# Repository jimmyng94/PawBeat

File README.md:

# PawPulse

PawPulse is an [open-source](https://github.com/jimmyng94/PawPulse/blob/master/LICENSE) pet health monitoring project developed by Engineering MSc students at the University Of Glasgow using a Raspberry Pi. The main functions that the project provide are:
- Heartbeat Monitoring
- Pedometer
- Live data display through a [website](https://tymonherzyk.github.io/PawPulseWeb/)

Currently, the development of the project is only intended for use on a dog. Usage on other pets will require further testing.

## Project Architecture

#### Hardware
All the sensors along with the raspberry will be attached to a dog harness to collect and process the data before posting the data to the web page. Therefore, the PCB is split into 2 individual boards. The 1st board is a PiHat where the [IMU](https://www.st.com/resource/en/datasheet/lsm6ds3.pdf) is located. The 2nd board contains the [ADC](http://www.ti.com/lit/ds/symlink/ads1015.pdf) and is located beside the microphone. Both boards are using I2C to communicate with the Raspberry Pi.

#### Software
The PawPulse software is split into two main files **pawpulse.cpp** and **pawpulseWebClient.cpp**. The pawpulse file is responsible for aquiring data for the dog's heartbeat and step count from the corresponding hardware. Once the data has been aquired through the getBPM() and getStep() functions it is then passed to the writeBPM() and writeSTEP() functions. These functions sort the data into the correct JSON format and pass it to the pawpulseWebClient.cpp file through named pipes bpm_fifo and step_fifo. The pawpulseWebClient file is responsible for uploading the data to the PawPulse website through the PubNub API. Threading has been used throughout the software to allow both processes (bpm and step) to work at the same time.  

#### Website
A website has been built in order to test the web capabilities of this project. The website has been designed to function as a profesional space in which the data from the PawPulse system can be displayed to users in real-time. The website has been built using HTML, CSS and JavaScript languages. To display data in real-time it utlises libraries such as PubNub API and EON. The website has also been built to be responsive and hence can be viewed safely on phone and monitors. Example screenshots from the "Live Data" page are given below:

The PawPulse website is hosted at https://tymonherzyk.github.io/PawPulseWeb/

#### Guides
Further information as well as in-depth installation and development guides for this project can be found on our Github [Wiki](https://github.com/jimmyng94/PawPulse/wiki) Page.

## Quick Installation
A full in-depth installation guide is available in our [wiki](https://github.com/jimmyng94/PawPulse/wiki/Installation-Guide).

#### 1. Clone PawPulse github repository
On the main repository page, click the green "Clone or Download" button, copy the address that drops down. In your chosen directory clone the PawPulse repository by running the folowing code:
```
git clone *copied address*
```
#### 2. Install required libraries
Install the required libraries (see the wiki for more information):
* ADS1015 Library
* LSM6DS3 Library
* Fir1 Library
* PubNub c-core
* WiringPi

#### 3. Make the pawpulse.cpp executable
To make the pawpulse executable file navigate into the "Software" folder and use the "CMakeLists.txt" file. This is done by running the following code:
```
cmake .
make
```
A new executable with the name **pawpulse** should now be available in the "Software" folder.

#### 4. Make the pawpulseWebClient.cpp executable
To make the pawpulseWebClient executable file navigate into the "Software" folder and use the "pawpulseWebClient.mk" makefile. This is done by running the following code:
```
make -f pawpulseWebClient.mk
```
A new executable with the name **pawpulseWebClient** should now be available in the "Software" folder.

#### 5. Run software
To run both executables simply run the following code in the "Software" folder using two seprate command lines:
```
./pawpulseWebClient
```
```
./pawpulse
```
## Additional Functionality
Recommendations of possible functions that could be added in the future: 
- Automated execution of the PawPulse software.
- Live heartbeat playback allowing the owner to hear their pet's heartbeat and make it more convenient for a veterinarian to monitor pets
- GPS tracking
- Health diagnoses and recommendations
- Personalised website login
- Phone application development for convenience

## Demonstration
A demonstration of the real-time application and operation of the PawPulse software is available on the PawPulse [Youtube Channel](https://www.youtube.com/channel/UC-eADsYPdyjXFOSjoH-YVWg). The demonstration shows the software being executed and the data being uploaded to the PawPulse website in real-time.

Video Link - https://www.youtube.com/watch?v=mI9MpOQwHOM

## Social Media
- [Instagram](https://www.instagram.com/paw_pulse/)
- [Youtube](https://www.youtube.com/channel/UC-eADsYPdyjXFOSjoH-YVWg)
- [Twitter](https://twitter.com/paw_pulse)

## Authors 
- [Maggie Wood](https://github.com/maggwood) - Data acquisition and data filtering
- [Ng Jing Ming](https://github.com/jimmyng94) - Hardware and hardware/software communication
- [Tymon Herzyk](https://github.com/tymonherzyk) - IPC, web client and website

## Disclaimer
Disruption due to COVID-19 has prohibited us from running any actual tests on our test dog. Thus, this project is not guaranteed to work on a dog. Testing was only done using a human heartbeat that was collected before the disruption. In the future we hope to be able to test it on a real pet and collect more data to improve our algorithm. Thank you for your understanding.

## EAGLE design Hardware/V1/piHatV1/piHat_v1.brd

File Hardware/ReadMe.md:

# Hardware
Hardware development of this project went through a few development and testing to determine the best circuit used for this project. 
This project requires an analog to digital converter to convert the analog microphone signal and an inertial measurement unit for pedometer function. 
The selected component used for version 1 of this project is listed below.
The schematic, board design and PCB mask are included in the newest version.  

## Version 0 (Concept)
- Mic signal is passed through a 4th order Low pass filter that filters noise above 1kHz. Used a [LM324N](http://www.ti.com/lit/ds/symlink/lm324-n.pdf). All the components are located in MicBOB_V0. 
- The IMU selected is attached on a PiHat. Fairly straight forward
###### Problems
- The Low pass filter seems to be attenuating the signal and no signal reaches the ADC.
- Missing power line to the VCC of the IMU.

## Version 1 (Prototype A)
- Removed the Low Pass Filter and used the ADS1014 Programmable Gain Amplifier(PGA) to amplify the signal from the microphone.
- Added a diode for reverse voltage protection.
- Added a trace to supply power to the IMU.

| Part | Quantity|
|-----| :-----: |
|Raspberry Pi | 1|
|[ADC ADS1014](http://www.ti.com/lit/ds/symlink/ads1015.pdf)|1|
|[IMU LSM6DS3](https://www.st.com/resource/en/datasheet/lsm6ds3.pdf)|1|
|6mm Microphone|1|
|1206 0.1uf Capacitor |2|
|5K Resistor|4|
|1N4148 Diode|1|
|20-pin Female Header|1|
|6-way header Molex connector|2|
|6-way shell Molex connector|2|
|M2.5 Standoffs	|4|
|M2.5 Screws	|4|

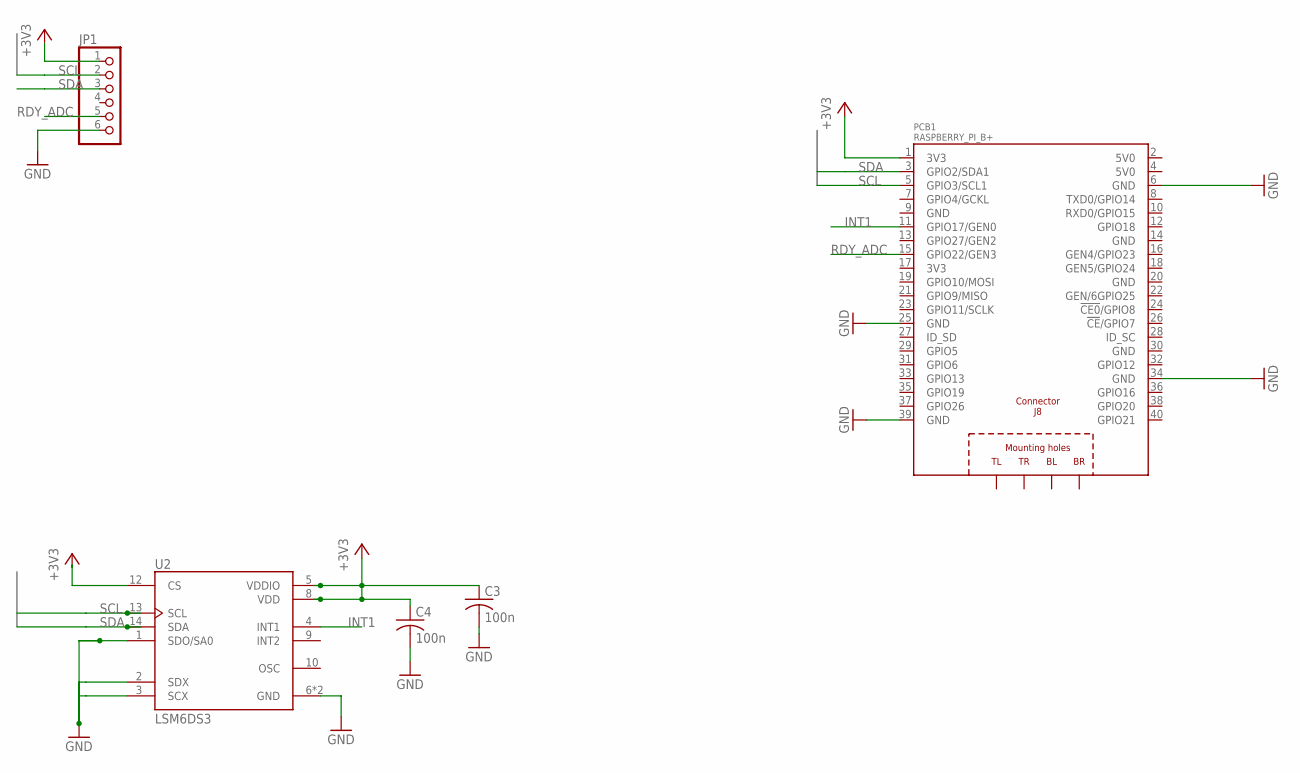
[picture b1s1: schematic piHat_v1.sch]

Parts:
C3, C4: 100n; C1206
JP1: PINHD-1X6; 1X06
PCB1: RASPBERRY_PI_B+
U2: LSM6DS3; PQFN50P300X250X86-14N

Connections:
+3V3: C3.1, C4.1, JP1.1, PCB1.1 (3V3), U2.5 (VDDIO), U2.8 (VDD), U2.12 (CS)
GND: C3.2, C4.2, JP1.6, PCB1.6 (GND), PCB1.25 (GND), PCB1.39 (GND), U2.1 (SDO/SA0), U2.2 (SDX), U2.3 (SCX), U2.6 (GND), U2.7 (GND)
GND@7: PCB1.34 (GND)
INT1: PCB1.11 (GPIO17/GEN0), U2.4 (INT1)
RDY_ADC: JP1.5, PCB1.15 (GPIO22/GEN3)
SCL: JP1.2, PCB1.5 (GPIO3/SCL1), U2.13 (SCL)
SDA: JP1.3, PCB1.3 (GPIO2/SDA1), U2.14 (SDA)

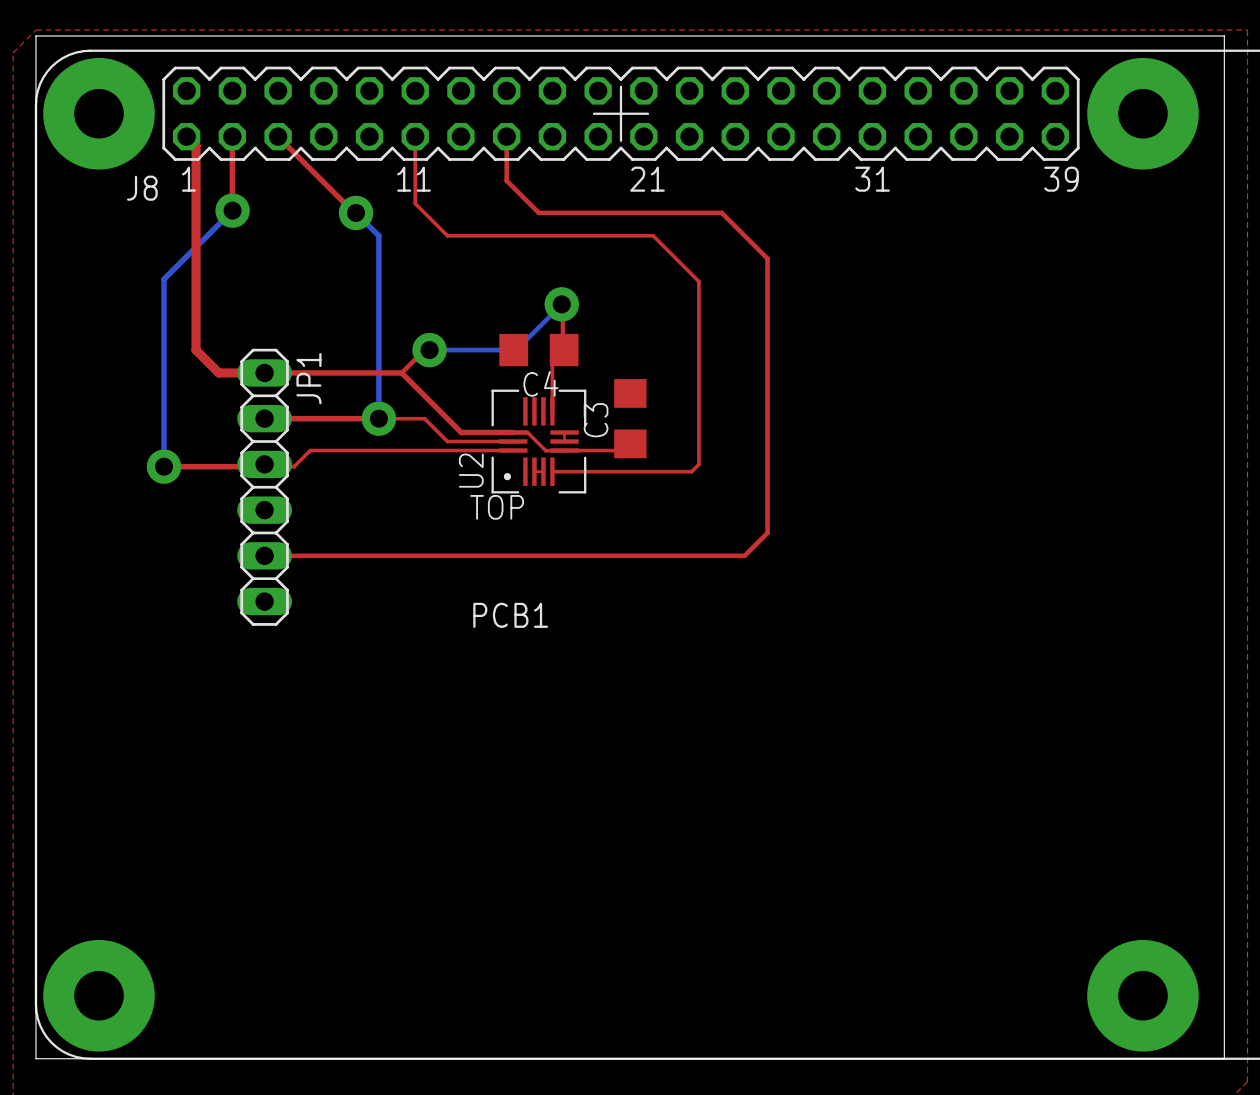
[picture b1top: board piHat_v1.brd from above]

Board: 2 copper layers, 66.0 x 56.8 mm, 5 parts (0 on the bottom side), 6 nets.

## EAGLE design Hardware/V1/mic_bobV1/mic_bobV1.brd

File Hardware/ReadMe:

Contain all the version of sensor and testing to main board intergration

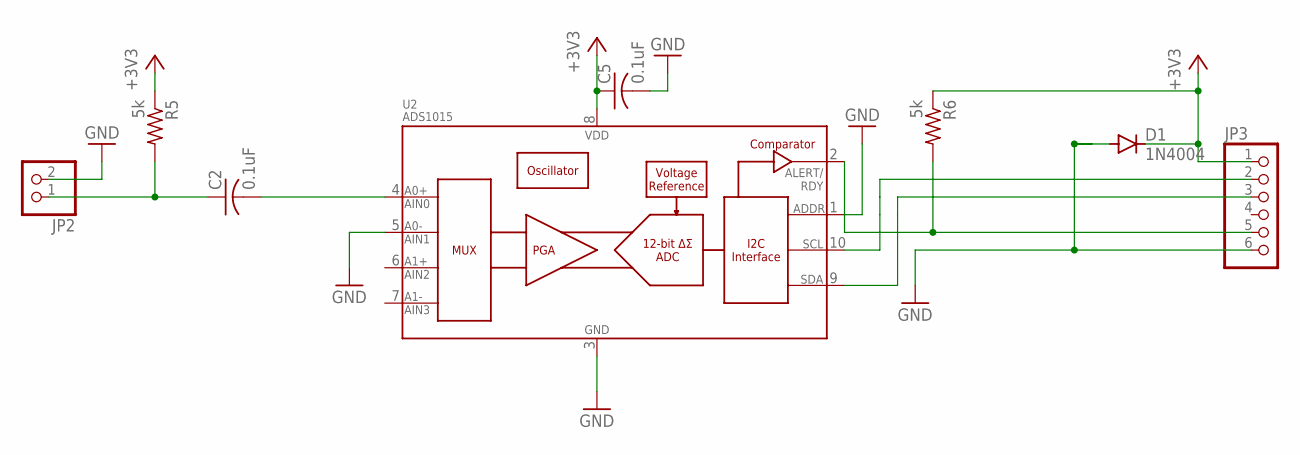
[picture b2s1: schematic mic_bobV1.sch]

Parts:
C2, C5: 0.1uF; C1206
D1: 1N4004; DO41-10
JP2: PINHD-1X2; 1X02
JP3: PINHD-1X6; 1X06
R5, R6: 5k; 0207/10
U2: ADS1015; MSOP10

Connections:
+3V3: C5.1, D1.C, JP3.1, R5.1, R6.1, U2.8 (VDD)
GND: C5.2, D1.A, JP2.2, JP3.6, U2.1 (ADDR), U2.3 (VSS), U2.5 (AIN1)
unnamed: C2.1, JP2.1, R5.2
unnamed: C2.2, U2.4 (AIN0)
unnamed: JP3.5, R6.2, U2.2 (ALERT/RDY)
unnamed: JP3.2, U2.10 (SCL)
unnamed: JP3.3, U2.9 (SDA)

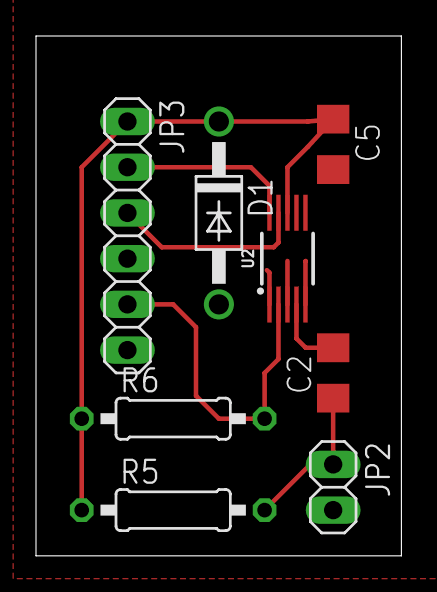
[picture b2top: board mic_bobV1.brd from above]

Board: 2 copper layers, 20.3 x 28.9 mm, 8 parts (0 on the bottom side), 7 nets.

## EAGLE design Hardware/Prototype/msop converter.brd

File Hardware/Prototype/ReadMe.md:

# Hardware Development
* After some consideration of device that are suitable for this project there are the ADS1014 is selected and the LSM6DS3 is selected. 
* To test the ADC a breakoutboard (msop10.brd) is develop for quick testing.
* The IMU used for initial testing is purchased from [sparkfun](https://www.sparkfun.com/products/13339)

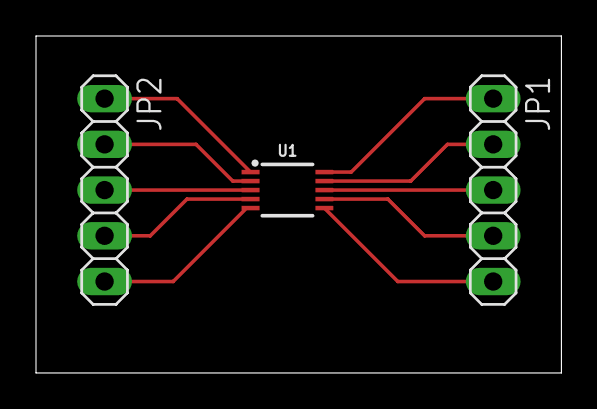
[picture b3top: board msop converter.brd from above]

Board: 2 copper layers, 29.2 x 18.7 mm, 3 parts (0 on the bottom side), 10 nets.

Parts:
JP1, JP2: 1X05
U1: ADS1015; MSOP10

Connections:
unnamed: JP2.1, U1.1
unnamed: JP2.2, U1.2
unnamed: JP2.3, U1.3
unnamed: JP2.4, U1.4
unnamed: JP2.5, U1.5
unnamed: JP1.1, U1.10
unnamed: JP1.2, U1.9
unnamed: JP1.3, U1.8
unnamed: JP1.4, U1.7
unnamed: JP1.5, U1.6

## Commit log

2020-02-05 Add files via upload
    Slides for initial presentation as given on the 29/01/2020
2020-02-05 Create mic2i2s
    Code for extracting audio from microphone and processing
2020-02-19 Update and rename mic2i2s to mic2i2c
    Added wiring pi library
2020-02-19 Create Hardware
    Hardware version control
2020-02-19 Create Prototype
2020-02-19 Update and rename Prototype to ReadMe
    correcting error
2020-02-19 Create Breakout board
2020-02-21 Update mic2i2c
2020-02-24 library for lsm6ds3
2020-02-26 Update mic2i2c.cpp
    Reads data from ADC, in while loop
2020-02-26 Update acc_test_trans.cpp
    back to basic
2020-02-27 Update SparkFunLSM6DS3.cpp
    revert back to to original with minimal change only to the i2c section
2020-02-27 Delete acc_test_trans.cpp
    not useful anymore
2020-02-27 Update LSM6DS3_test.cpp
    test_code Working
2020-02-27 Rename Pedometer/LSM6DS3_test.cpp to Pedometer/acc_test/acc_test.cpp
2020-02-27 Rename SparkFunLSM6DS3.h to LSM6DS3.h
2020-03-04 Update mic2i2c.cpp
    Reads 12000 samples of voltage from microphone, stores in buffer, then prints values to file titled 'heartbeat_30'.
2020-03-04 Update pedometer_test.cpp
    syntax correction
2020-03-07 Create Microphone Breakout
2020-03-07 Delete Microphone Breakout
    Replaced by uploading the actual .sch file
2020-03-07 Create PCB
2020-03-07 Add files via upload
    Used for testing ADS1014
2020-03-09 Create error report
2020-03-10 Create cmaketest.txt
    Cmake test file for pubnub library
2020-03-11 Update LSM6DS3.cpp
    attempt to add interrupt pin 1
2020-03-11 Create coefficient generator.py
    Creates coefficients for FIR signal processing of heart rate signal generated with PawPulse.
2020-03-11 Update liveData.html
    fix issue where "bpmMsg" and "stepMsg" can now display eon object as string
2020-03-11 Delete subscribe_publish_callback_sample.cpp
    Will work on this in separate branch
2020-03-11 Delete README.md
    Will work on this in separate branch
2020-03-11 Delete pubnub.hpp
    Will work on this in separate branch
2020-03-12 Update README.md
    Added website link
2020-03-13 Update Interrupt.cpp
    correcting file for mic
2020-03-16 Update subscribe_publish_callback_sample.cpp
    Version 2: Update to include FIFO IPC for acquiring message data from pipeWriter script.
    Working as of 16/03/2020
2020-03-16 Delete subscribe_publish_callback_sample.cpp
    Outdated: Look for file in pubnub/pawpulse_samples
2020-03-16 Delete pipeReader.cpp
    Outdated new version can be found in IPC folder
2020-03-16 Delete pipeWriter.cpp
    Outdated, find new version in IPC folder
2020-03-19 Rename coefficient generator.py to coefficient_generator.py
2020-03-20 Update processing.cpp
    Added code for bpm
2020-03-20 Update processing.cpp
    Added acc processing
2020-03-20 Update processing.cpp
    1st integration/ broken
2020-04-14 Create LICENSE
2020-04-14 Update ReadMe.md
    V1 update
2020-04-15 Update LSM6DS3.cpp
    Corrected spelling mistake at line 514
2020-04-16 Update fifo file paths
2020-04-17 Kept includes needed
2020-04-17 Rename Pedometer/CMakeLists.txt to LSM6DS3_Lib/CMakeLists.txt
2020-04-17 Rename Pedometer/LSM6DS3.cpp to LSM6DS3_Lib/LSM6DS3.cpp
2020-04-17 Rename Pedometer/LSM6DS3.h to LSM6DS3_Lib/LSM6DS3.h
2020-04-17 Rename heartrate/CMakeLists.txt to ADS_Lib/CMakeLists.txt
2020-04-17 Rename heartrate/ADS1015.cpp to ADS_Lib/ADS1015.cpp
2020-04-17 Rename heartrate/ADS1015.h to ADS_Lib/ADS1015.h
2020-04-17 Rename processing.cpp to pawpulse.cpp
2020-04-17 Rename webClient/sendDataClient/sendDataClient.cpp to Software/PawPulseWebClient.cpp
2020-04-17 Rename webClient/sendDataClient/sendDataClient.mk to Software/PawPulseWebClient.mk
2020-04-17 Rename website/index.html to Software/Website/index.html
2020-04-17 Rename website/liveData.html to Software/Website/liveData.html
2020-04-17 Rename website/style.css to Software/Website/style.css
2020-04-17 Rename website/README.md to Software/Website/README.md
2020-04-17 Rename LSM6DS3_Lib/LSM6DS3.cpp to Software/Libraries/LSM6DS3/LSM6DS3.cpp
2020-04-17 Rename LSM6DS3_Lib/CMakeLists.txt to Software/Libraries/LSM6DS3/CMakeLists.txt
2020-04-17 Rename LSM6DS3_Lib/LSM6DS3.h to Software/Libraries/LSM6DS3/LSM6DS3.h
2020-04-17 Rename ADS_Lib/ADS1015.cpp to Software/Libraries/ADS1015/ADS1015.cpp
2020-04-17 Rename ADS_Lib/ADS1015.h to Software/Libraries/ADS1015/ADS1015.h
2020-04-17 Rename ADS_Lib/CMakeLists.txt to Software/Libraries/ADS1015/CMakeLists.txt
2020-04-17 Rename temp/ads_120_C.txt to Software/ads_120_C.txt
2020-04-17 Rename temp/pawpulse.cpp to Software/pawpulse.cpp
2020-04-17 Rename PawPulseWebClient.cpp to pawpulseWebClient.cpp
2020-04-17 Rename PawPulseWebClient.mk to pawpulseWebClient.mk
2020-04-18 Update to final version
2020-04-18 Change file path for named pipes
2020-04-18 Update file paths with Libraries/c-core
2020-04-19 Rename ADC and IMU acquisition/CMakeLists.txt to Software/Previous Versions and Testing/ADC and IMU acquisition/CMakeLists.txt
2020-04-19 Rename ADC and IMU acquisition/threadedAccq.cpp to Software/Previous Versions and Testing/ADC and IMU acquisition/threadedAccq.cpp
2020-04-19 Rename ADC and IMU acquisition/imuDataLogger/CMakeLists.txt to Software/Previous Versions and Testing/ADC and IMU acquisition/imuDataLogger/CMakeLists.txt
2020-04-19 Rename ADC and IMU acquisition/imuDataLogger/imuAccq.cpp to Software/Previous Versions and Testing/ADC and IMU acquisition/imuDataLogger/imuAccq.cpp
2020-04-19 Rename ADC and IMU acquisition/imuDataLogger/Data_collected/3x.txt to Software/Previous Versions and Testing/ADC and IMU acquisition/imuDataLogger/Data_collected/3x.txt
2020-04-19 Rename ADC and IMU acquisition/imuDataLogger/Data_collected/3y.txt to Software/Previous Versions and Testing/ADC and IMU acquisition/imuDataLogger/Data_collected/3y.txt
2020-04-19 Rename ADC and IMU acquisition/imuDataLogger/Data_collected/3Z.txt to Software/Previous Versions and Testing/ADC and IMU acquisition/imuDataLogger/Data_collected/3Z.txt
2020-04-19 Rename ADC and IMU acquisition/imuDataLogger/Data_collected/0Z.txt to Software/Previous Versions and Testing/ADC and IMU acquisition/imuDataLogger/Data_collected/0Z.txt
2020-04-19 Rename ADC and IMU acquisition/imuDataLogger/Data_collected/0x.txt to Software/Previous Versions and Testing/ADC and IMU acquisition/imuDataLogger/Data_collected/0x.txt
2020-04-19 Rename ADC and IMU acquisition/imuDataLogger/Data_collected/0y.txt to Software/Previous Versions and Testing/ADC and IMU acquisition/imuDataLogger/Data_collected/0y.txt
2020-04-19 Rename ADC and IMU acquisition/imuDataLogger/Data_collected/1Z.txt to Software/Previous Versions and Testing/ADC and IMU acquisition/imuDataLogger/Data_collected/1Z.txt
2020-04-19 Rename ADC and IMU acquisition/imuDataLogger/Data_collected/1x.txt to Software/Previous Versions and Testing/ADC and IMU acquisition/imuDataLogger/Data_collected/1x.txt
2020-04-19 Rename ADC and IMU acquisition/imuDataLogger/Data_collected/1y.txt to Software/Previous Versions and Testing/ADC and IMU acquisition/imuDataLogger/Data_collected/1y.txt
2020-04-19 Rename ADC and IMU acquisition/imuDataLogger/Data_collected/2Z.txt to Software/Previous Versions and Testing/ADC and IMU acquisition/imuDataLogger/Data_collected/2Z.txt
2020-04-19 Rename ADC and IMU acquisition/imuDataLogger/Data_collected/2x.txt to Software/Previous Versions and Testing/ADC and IMU acquisition/imuDataLogger/Data_collected/2x.txt
2020-04-19 Rename ADC and IMU acquisition/imuDataLogger/Data_collected/2y.txt to Software/Previous Versions and Testing/ADC and IMU acquisition/imuDataLogger/Data_collected/2y.txt
2020-04-19 Rename Pedometer/README.md to Software/Previous Versions and Testing/Pedometer/README.md
2020-04-19 Rename Pedometer/pedometer_test.cpp to Software/Previous Versions and Testing/Pedometer/pedometer_test.cpp
2020-04-19 Rename Pedometer/acc_test/README.md to Software/Previous Versions and Testing/Pedometer/acc_test/README.md
2020-04-19 Rename Pedometer/acc_test/CMakeLists.txt to Software/Previous Versions and Testing/Pedometer/acc_test/CMakeLists.txt
2020-04-19 Rename Pedometer/acc_test/acc_test.cpp to Software/Previous Versions and Testing/Pedometer/acc_test/acc_test.cpp
2020-04-19 Rename heartrate/README.md to Software/Previous Versions and Testing/Heartrate/README.md
2020-04-19 Rename heartrate/error report to Software/Previous Versions and Testing/Heartrate/error report
2020-04-19 Rename heartrate/mic2i2c.cpp to Software/Previous Versions and Testing/Heartrate/mic2i2c.cpp
2020-04-19 Rename heartrate/Examples/CMakeLists.txt to Software/Previous Versions and Testing/Heartrate/Examples/CMakeLists.txt
2020-04-19 Rename heartrate/Examples/Interrupt.cpp to Software/Previous Versions and Testing/Heartrate/Examples/Interrupt.cpp
2020-04-19 Rename heartrate/signal_processing/README.md to Software/Previous Versions and Testing/Heartrate/signal_processing/README.md
2020-04-19 Rename heartrate/signal_processing/FIR_filter.py to Software/Previous Versions and Testing/Heartrate/signal_processing/FIR_filter.py
2020-04-19 Rename heartrate/signal_processing/ads_data.txt to Software/Previous Versions and Testing/Heartrate/signal_processing/ads_data.txt
2020-04-19 Rename heartrate/signal_processing/ads_data70.txt to Software/Previous Versions and Testing/Heartrate/signal_processing/ads_data70.txt
2020-04-19 Rename heartrate/signal_processing/coefficient_generator.py to Software/Previous Versions and Testing/Heartrate/signal_processing/coefficient_generator.py
2020-04-19 Rename heartrate/signal_processing/filter.cpp to Software/Previous Versions and Testing/Heartrate/signal_processing/filter.cpp
2020-04-19 Rename heartrate/signal_processing/hr_coeff.dat to Software/Previous Versions and Testing/Heartrate/signal_processing/hr_coeff.dat
2020-04-19 Rename heartrate/signal_processing/process.py to Software/Previous Versions and Testing/Heartrate/signal_processing/process.py
2020-04-19 Rename heartrate/signal_processing/processing.cpp to Software/Previous Versions and Testing/Heartrate/signal_processing/processing.cpp
2020-04-19 Update picture paths
2020-04-19 Move images to Media folder
2020-04-19 Moved to Other/Media

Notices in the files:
parts and their libraries:
SparkFun-IC-Conversion: Licensing: Creative Commons ShareAlike 4.0 International - https://creativecommons.org/licenses/by-sa/4.0
